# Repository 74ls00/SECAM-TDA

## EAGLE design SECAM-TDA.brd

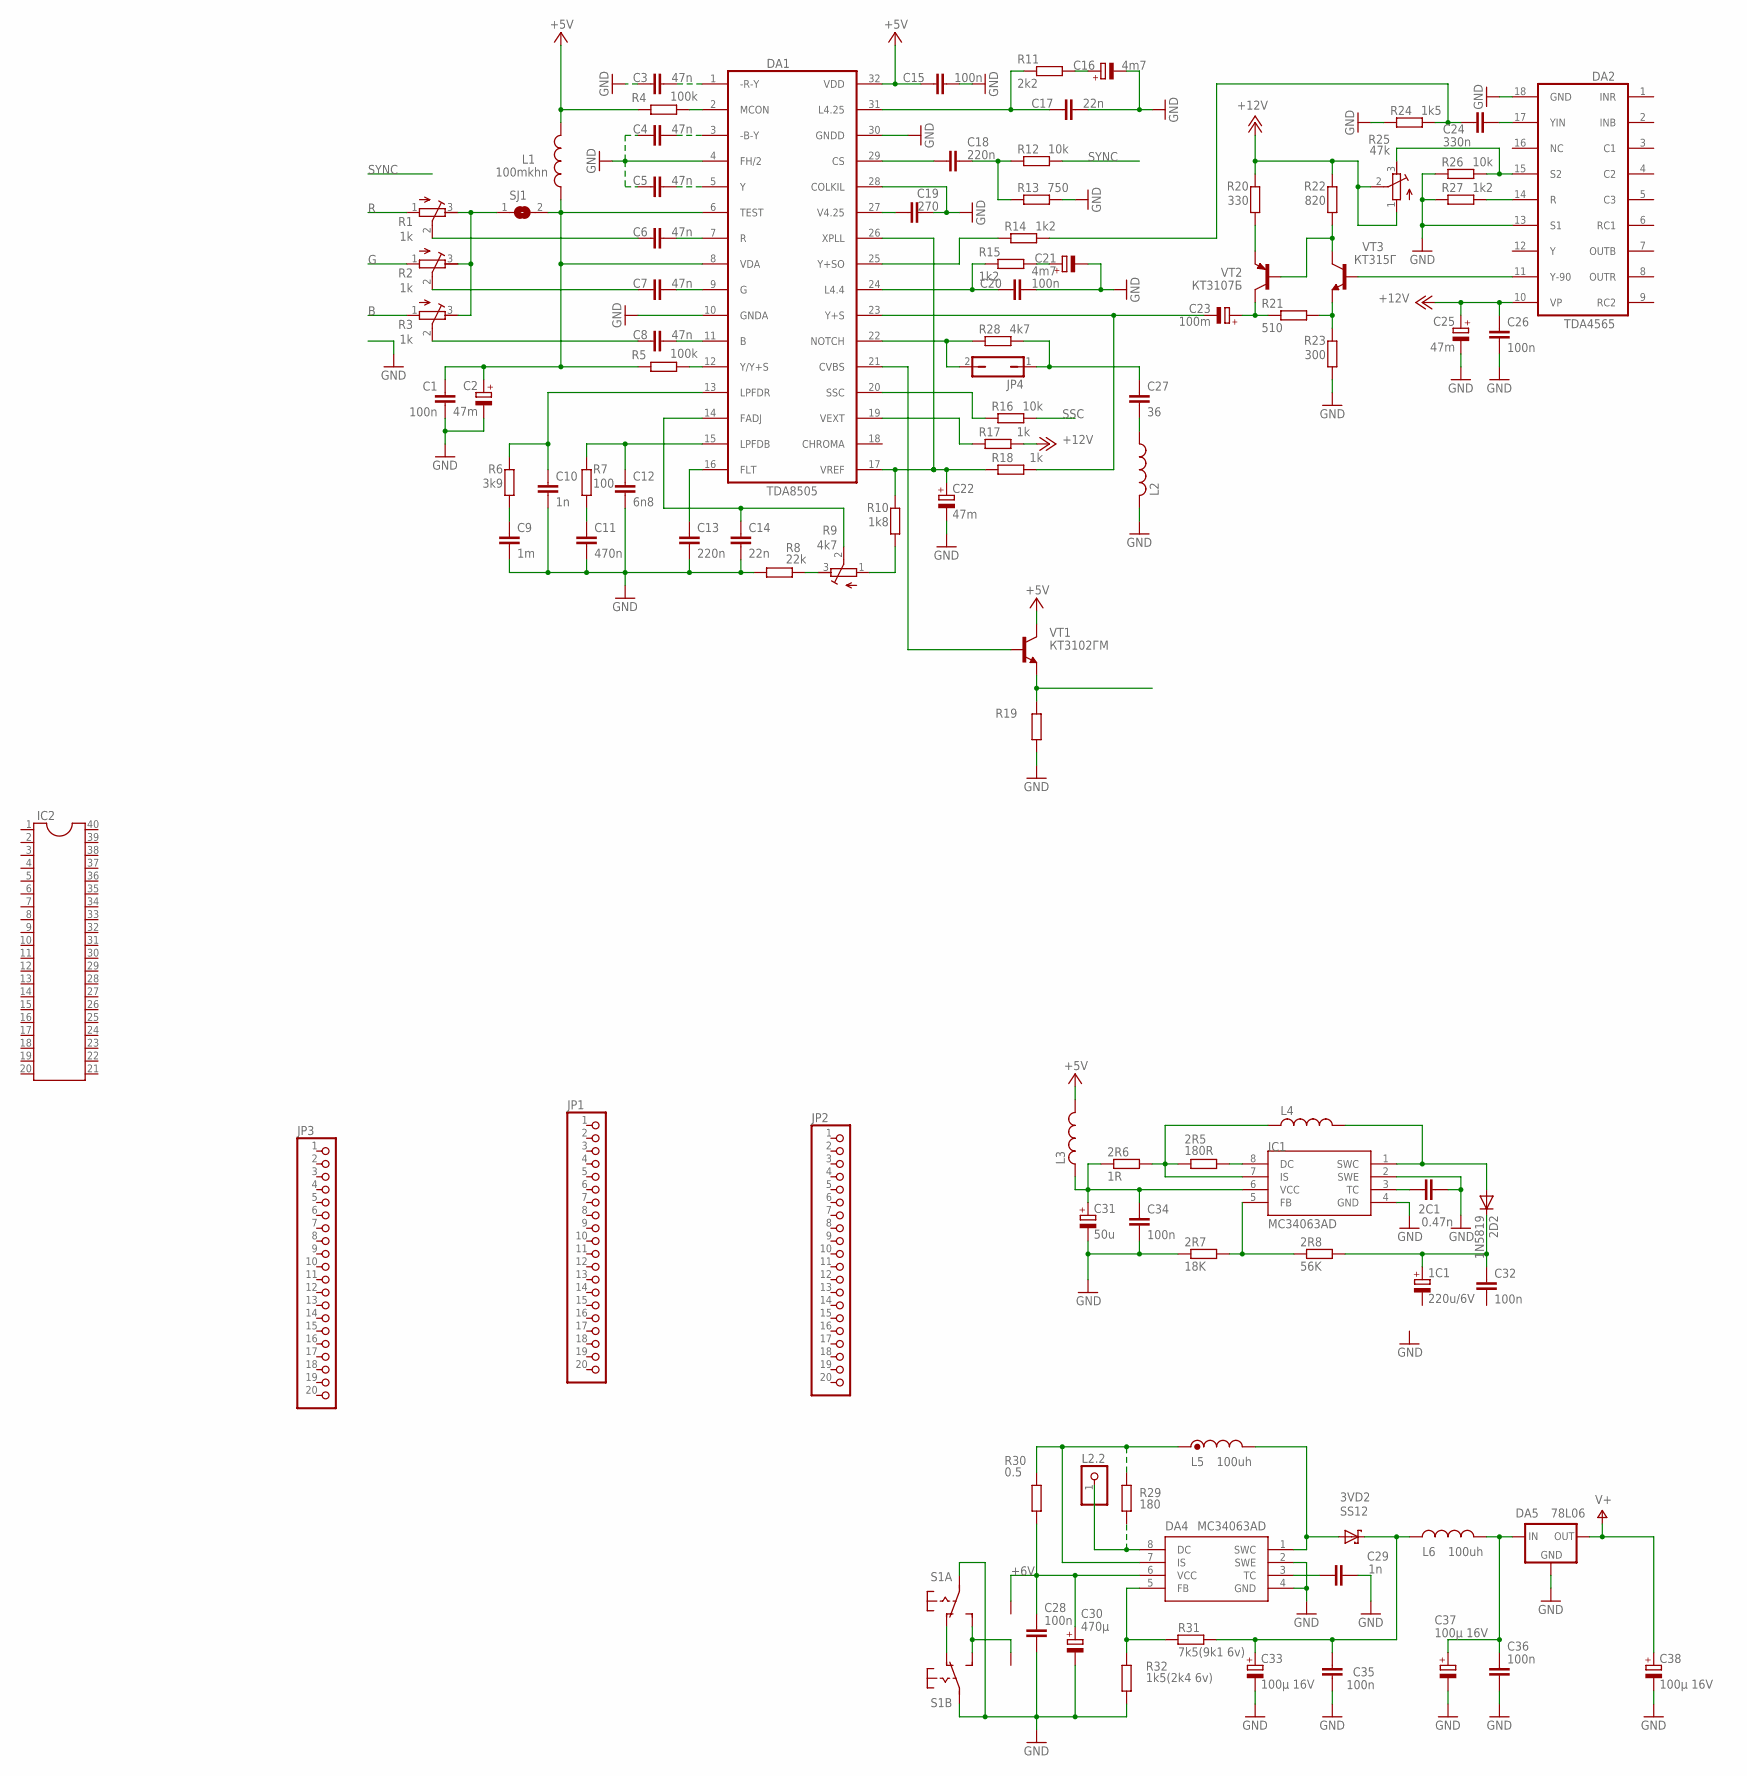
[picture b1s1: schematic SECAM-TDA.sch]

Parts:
1C1: 220u/6V; E3,5-8
2C1: 0.47n; C0805K
2D2: 1N5819; SMB
2R5: 180R; R0805
2R6: 1R; R0805
2R7: 18K; R0805
2R8: 56K; R0805
3VD2: SS12; SMB
C1, C15, C20, C26, C28, C35, C36: 100n; C0805
C2, C22, C25: 47m; E2,5-5
C3, C4, C5, C6, C7, C8: 47n; C025-025X050
C9: 1m; C025-025X050
C10: 1n; C025-025X050
C11: 470n; C025-025X050
C12: 6n8; C025-025X050
C13, C18: 220n; C025-025X050
C14, C17: 22n; C025-025X050
C16, C21: 4m7; E2,5-5
C19: 270; C025-025X050
C23: 100m; E2,5-5
C24: 330n; C025-025X050
C27: 36; C0805
C29: 1n; C0805
C30: 470µ; RCL_E2,5-7
C31: 50u; E2,5-6
C32, C34: 100n; C0805K
C33, C37, C38: 100µ 16V; RCL_E2,5-5
DA1: TDA8505; PDIP32
DA2: TDA4565; DIL18
DA4: MC34063AD; SOIC8
DA5: 78L06; SOT89R
IC1: MC34063AD; SOIC8
IC2: DIL40
JP1, JP2, JP3: PINHD-1X20; 1X20
JP4: JP1Q; JP1
L1: 100mkhn; 0207/10
L2: L0204/5; 0204/5
L2.2: PINHD-1X1; 1X01
L3, L4: L0204/7; 0204/7
L5: 100uh; 0204/7
L6: 100uh; 0207/10
R1, R2, R3: 1k; RTRIM3296W
R4: 100k; R0805
R5: 100k; 0204/7
R6: 3k9; R0805
R7: 100; 0204/7
R8: 22k; R0805
R9: 4k7; RTRIM3296W
R10: 1k8; R0805
R11: 2k2; R0805
R12, R16, R26: 10k; R0805
R13: 750; R0805
R14: 1k2; 0207/10
R15, R27: 1k2; R0805
R17, R18: 1k; R0805
R19: R-EU_R0805; R0805
R20: 330; R0805
R21: 510; R0805
R22: 820; R0805
R23: 300; R0805
R24: 1k5; R0805
R25: 47k; RTRIM3296W
R28: 4k7; R0805
R29: 180; M0805
R30: 0.5; M1206
R31: 7k5(9k1 6v); M0805
R32: 1k5(2k4 6v); M0805
S1: SWITCH9X4
SJ1: SJ
U$5: B-
U$6: B+
VT1: КТ3102ГМ; TO92-EBC
VT2: КТ3107Б; TO92-BCE
VT3: КТ315Г; TO92-ECB

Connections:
+5V: C15.1, DA1.32 (VDD), L1.2, L3.2, R4.1, VT1.C
+6V: C28.1, C30.+, DA4.6 (VCC), R30.1, U$6.P$1
+12V: C25.+, C26.1, DA2.10 (VP), R17.2, R20.2, R22.2, R25.1 (A), R25.2 (S)
B: R3.1 (A)
G: R2.1 (A)
GND: 2C1.2, 2R7.1, C1.2, C2.-, C3.1, C4.1, C5.1, C9.2, C10.2, C11.2, C12.2, C13.2, C14.2, C15.2, C16.-, C17.2, C19.2, C20.2, C21.-, C22.-, C25.-, C26.2, C28.2, C29.2, C30.-, C31.-, C33.-, C34.2, C35.1, C36.2, C37.-, C38.-, DA1.4 (FH/2), DA1.10 (GNDA), DA1.28 (COLKIL), DA1.30 (GNDD), DA2.13 (S1), DA2.18 (GND), DA4.2 (SWE), DA4.4 (GND), DA5.3 (GND), DA5.4 (GND), IC1.2 (SWE), IC1.4 (GND), L2.1, R8.1, R13.2, R19.1, R23.1, R24.1, R26.1, R27.1, R32.1, S1.10, S1.20
unnamed: C3.2, DA1.1 (-R-Y)
unnamed: DA1.2 (MCON), R4.2
unnamed: C24.2, DA2.17 (YIN)
unnamed: C4.2, DA1.3 (-B-Y)
unnamed: C5.2, DA1.5 (Y)
unnamed: C1.1, C2.+, DA1.6 (TEST), DA1.8 (VDA), L1.1, R5.1, SJ1.2
unnamed: C6.1, R1.2 (S)
unnamed: C6.2, DA1.7 (R)
unnamed: C11.1, R7.1
unnamed: C7.1, R2.2 (S)
unnamed: C7.2, DA1.9 (G)
unnamed: C8.2, DA1.11 (B)
unnamed: C8.1, R3.2 (S)
unnamed: DA1.12 (Y/Y+S), R5.2
unnamed: C13.1, DA1.16 (FLT)
unnamed: C10.1, DA1.13 (LPFDR), R6.2
unnamed: R8.2, R9.3 (E)
unnamed: C9.1, R6.1
unnamed: C12.1, DA1.15 (LPFDB), R7.2
unnamed: C14.1, DA1.14 (FADJ), R9.2 (S)
unnamed: C22.+, DA1.17 (VREF), DA1.26 (XPLL), R10.2, R18.1
unnamed: C19.1, DA1.27 (V4.25)
unnamed: R9.1 (A), R10.1
unnamed: DA1.19 (VEXT), R17.1
unnamed: DA1.20 (SSC), R16.1
unnamed: DA1.21 (CVBS), VT1.B
unnamed: C23.-, DA1.23 (Y+S), R18.2
unnamed: C20.1, DA1.24 (L4.4), R15.1
unnamed: C21.+, R15.2
unnamed: C17.1, DA1.31 (L4.25), R11.1
unnamed: C24.1, R14.2, R24.2
unnamed: DA1.25 (Y+SO), R14.1
unnamed: C16.+, R11.2
unnamed: DA2.14 (R), R27.2
unnamed: DA2.15 (S2), R25.3 (E), R26.2
unnamed: C18.1, DA1.29 (CS)
unnamed: C18.2, R12.1, R13.1
unnamed: DA2.11 (Y-90), VT3.B
unnamed: R22.1, VT2.B, VT3.C
unnamed: R20.1, VT2.E
unnamed: R21.2, R23.2, VT3.E
unnamed: C23.+, R21.1, VT2.C
unnamed: R19.2, VT1.E
unnamed: C27.1, JP4.1, R28.2
unnamed: R1.3 (E), R2.3 (E), R3.3 (E), SJ1.1
unnamed: DA1.22 (NOTCH), JP4.2, R28.1
unnamed: 2C1.1, IC1.3 (TC)
unnamed: 2D2.A, IC1.1 (SWC), L4.2
unnamed: 2R5.1, 2R6.2, IC1.7 (IS), L4.1
unnamed: 2R5.2, IC1.8 (DC)
unnamed: 2R7.2, 2R8.1, IC1.5 (FB)
unnamed: DA4.8 (DC), L2.2.1, R29.1
unnamed: 1C1.+, 2D2.C, 2R8.2, C32.1
unnamed: 2R6.1, C31.+, C34.1, IC1.6 (VCC), L3.1
unnamed: C27.2, L2.2
unnamed: DA4.7 (IS), L5.1, R29.2, R30.2
unnamed: DA4.5 (FB), R31.1, R32.2
unnamed: 3VD2.A, DA4.1 (SWC), L5.2
unnamed: C29.1, DA4.3 (TC)
unnamed: 3VD2.C, C33.+, C35.2, L6.1, R31.2
unnamed: S1.12 (S), S1.22 (S), U$5.P$1
unnamed: S1.11 (O), S1.21 (O)
unnamed: C36.1, C37.+, DA5.1 (IN), L6.2
R: R1.1 (A)
SSC: R16.2
SYNC: R12.2
V+: C38.+, DA5.2 (OUT)

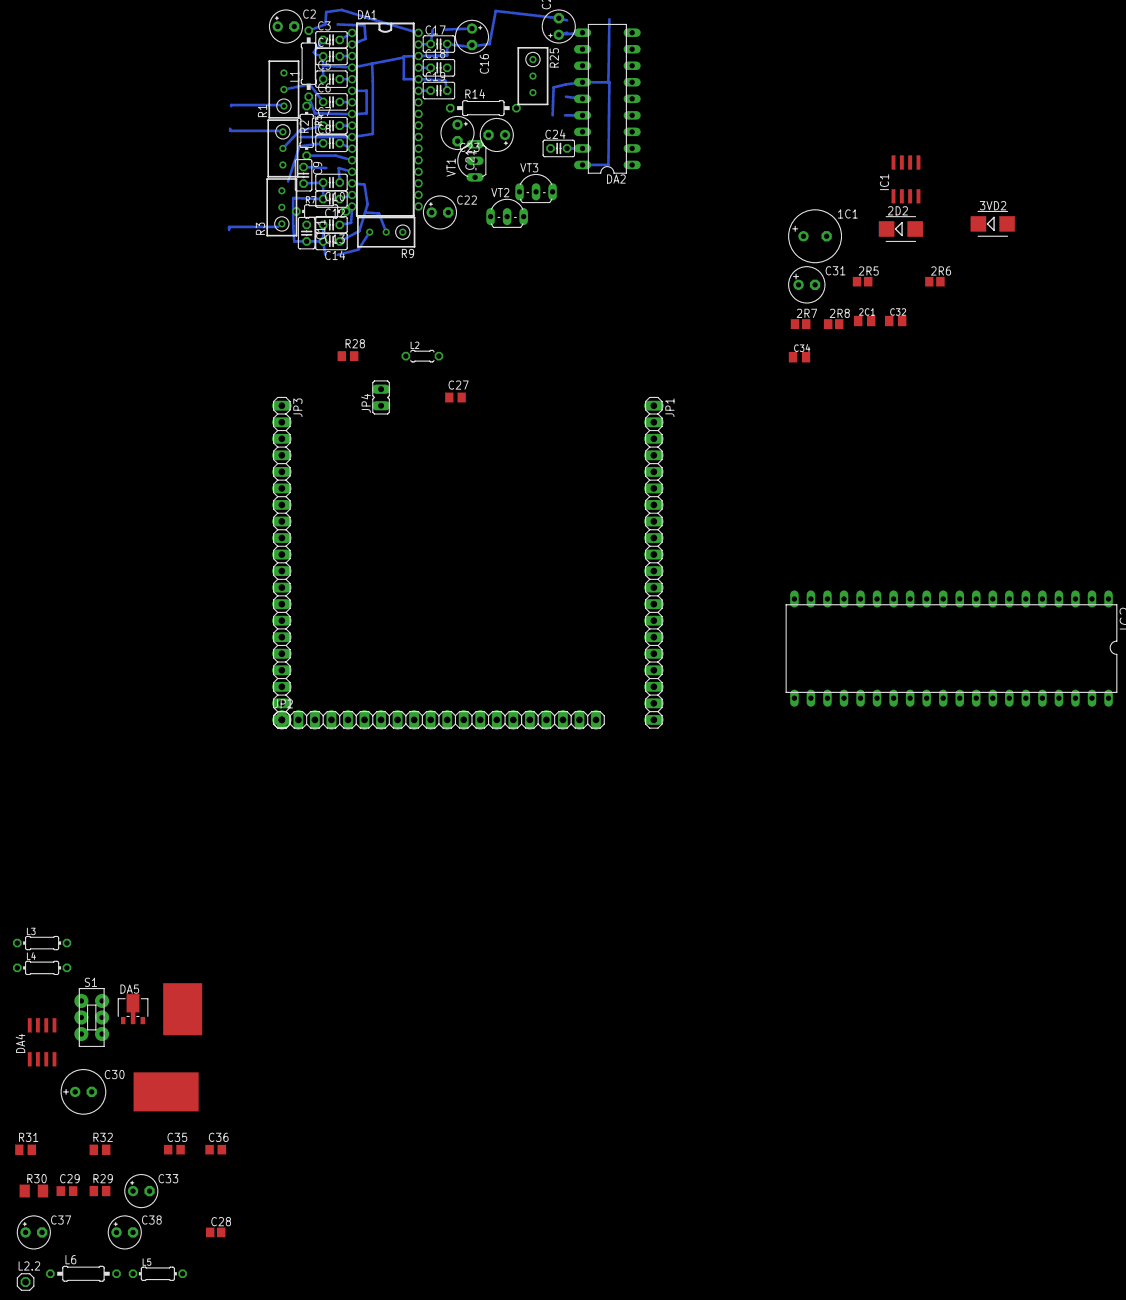
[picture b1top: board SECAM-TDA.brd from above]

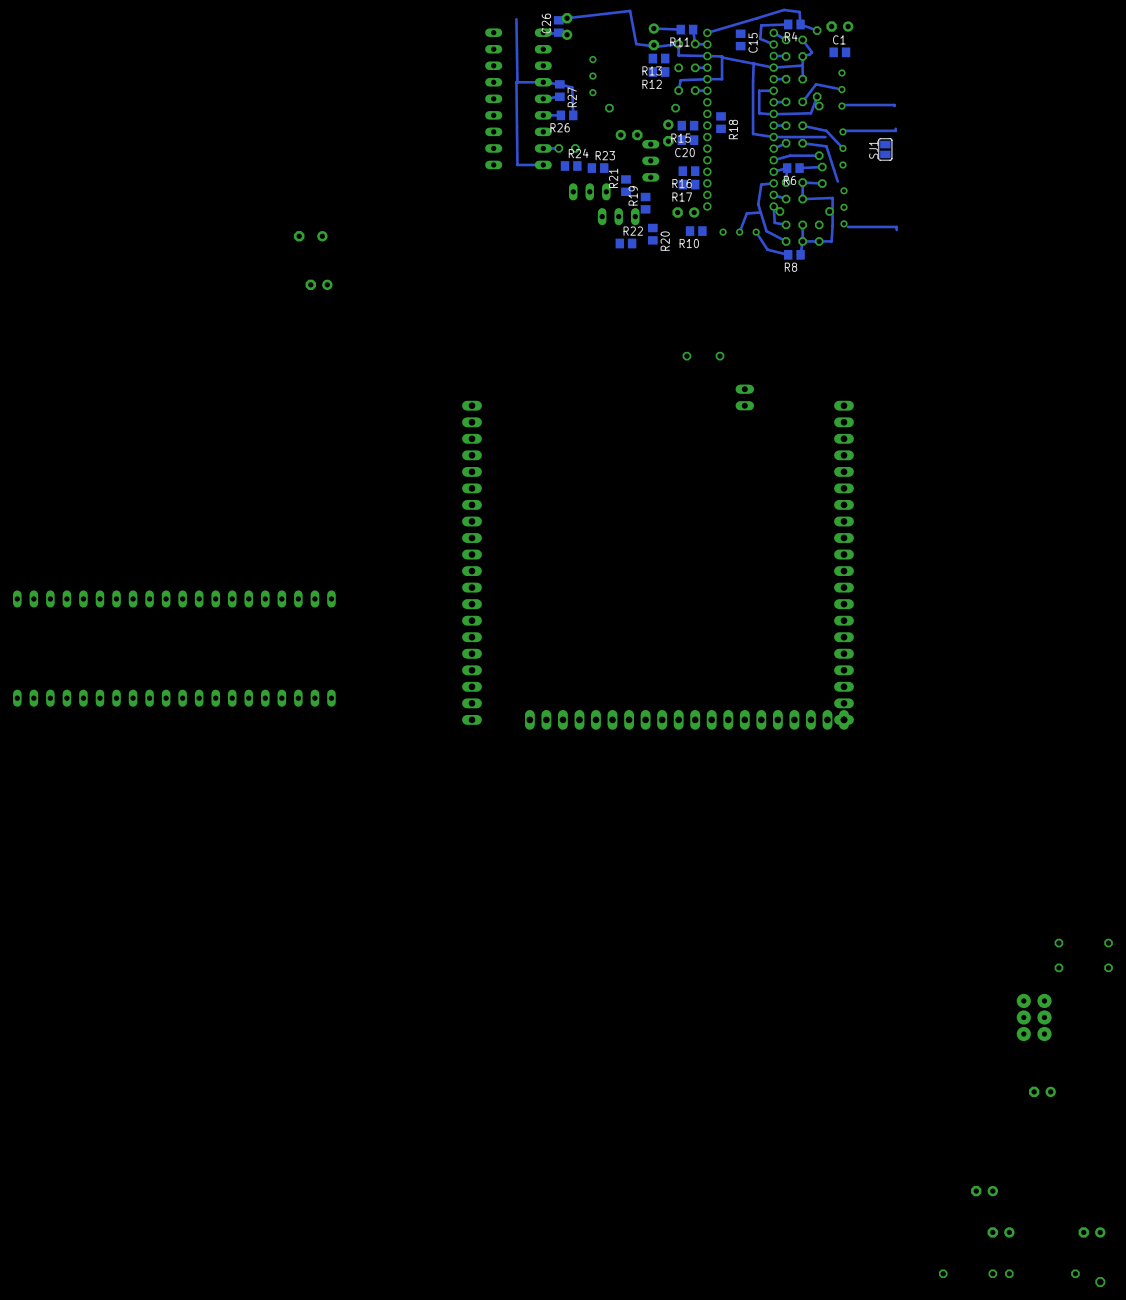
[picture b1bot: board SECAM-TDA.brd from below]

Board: 2 copper layers, 102 parts (24 on the bottom side), 68 nets.

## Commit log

2019-12-09 2019
